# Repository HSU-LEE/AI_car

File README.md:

# AICAR — 라즈베리 파이 자율주행 미니카

카메라 한 대로 흰 차선을 따라가고, 교차로·횡단보도·신호등·레고 사람·장애물에 반응하며,
`course.py`에 적은 순서대로 경기 코스를 완주하는 자율주행 RC카입니다.
맥에서 메뉴를 더블클릭하거나 `aicar` 명령 하나로 코드 업로드, 주행, 보정, 녹화 분석을 모두 할 수 있습니다.

---

## 주요 기능

| 분야 | 내용 |
|---|---|
| **차선 주행** | 화면 아래를 여러 띠로 나눠 흰 선을 찾고, 위치·방향 오차로 조향각을 계산 (`bands` / `pairs` / `track` 방식) |
| **코스 실행** | 교차로, 차선 끝, 횡단보도, 차선 끊김을 만날 때마다 `course.py`의 다음 동작 실행 (좌회전, 우회전, 유턴, 정지 등) |
| **인식** | 신호등(빨강/초록), 횡단보도, 레고 사람(TFLite 신경망), 정지 지점, 거리 센서 장애물 |
| **시작 버튼** | GPIO21 버튼: 한 번 누르면 출발 → 일시정지 → 다시 출발, 3초 꾹 누르면 대기 상태로 |
| **출발 전 조향 확인** | 버튼으로 출발할 때 앞바퀴를 왼쪽 → 오른쪽 → 중앙으로 움직여 서보 상태를 확인 |
| **안전 장치** | 모터 감시(루프가 멈추면 정지), 별도 감시 프로세스(프로그램이 죽어도 모터 정지), 맥 연결이 끊겨도 주행 유지 |
| **브라우저 화면** | 주행 중 인식 결과를 `http://<파이 IP>:8000`에서 실시간 확인, 웹에서 신호등·횡단보도·선 등록 |
| **기록과 분석** | 모든 주행의 기록 자동 저장, 녹화 영상을 맥에서 다시 분석(`replay`), 폐루프 시뮬레이터(`sim.py`) |
| **자동 보정** | 경기장에서 트랙 색, 초점, 조명, 차선 폭, 소실점, 카메라 중심을 한 번에 측정·저장 |

## 시스템 구성

```mermaid
flowchart LR
    Mac["맥<br/>Menu.command · aicar"] -- "SSH / rsync" --> Pi
    Mac -. "브라우저 :8000" .-> Pi
    subgraph Pi["라즈베리 파이 4 (lane_follow.py)"]
        Cam["카메라"] --> Detect["차선·표지 인식"]
        Detect --> Course["코스 실행<br/>course.py"]
        Course --> Steer["조향 · 속도"]
    end
    Steer --> Servo["조향 서보<br/>GPIO18"]
    Steer --> Motor["구동 모터<br/>TB6612 · GPIO13/23/24"]
    Sensor["거리 센서<br/>GPIO17"] --> Course
    Button["시작 버튼<br/>GPIO21"] --> Course
```

## 하드웨어와 배선

| 부품 | 파이 핀 | 비고 |
|---|---|---|
| 조향 서보 신호 | GPIO18 (12번) | 하드웨어 PWM 50Hz |
| 모터 드라이버 TB6612 PWMA | GPIO13 (33번) | 하드웨어 PWM 20kHz |
| TB6612 AIN1 / AIN2 | GPIO23 (16번) / GPIO24 (18번) | 방향 |
| TB6612 STBY, VCC | 3.3V | GND 공통 |
| 거리 센서 Sharp GP2Y0A21 | GPIO17 (11번) | 5V 전원 |
| 시작 버튼 | GPIO21 (40번) ↔ GND (39번) | 내부 풀업 |
| 카메라 | CSI | Picamera2 |

하드웨어 PWM을 쓰려면 `/boot/firmware/config.txt`에 `dtoverlay=pwm-2chan,pin=18,func=2,pin2=13,func2=4`가 필요합니다.
SD 카드 이미지는 [`os-image/`](os-image)의 스크립트로 만듭니다.

## 빠르게 시작하기

1. 맥과 파이를 같은 Wi-Fi에 연결합니다. 파이의 핫스팟(`10.42.0.1`)에 붙어도 됩니다. 주소는 자동으로 찾습니다.
2. **`Menu.command`** 를 더블클릭하면 모든 기능이 한국어 메뉴로 나옵니다.
3. 터미널을 쓴다면:

```bash
./aicar status
```

```bash
./aicar calibrate
```

```bash
./aicar go
```

- `aicar status`: 연결과 파이 상태 확인
- `aicar calibrate`: 경기장에서 한 번 자동 보정 (직선 차로 가운데에 차를 놓고)
- `aicar go`: 주행 시작 (코드를 자동으로 올린 뒤 실행). 버튼을 켜 두었다면 버튼을 눌러야 출발합니다.

멈출 때는 터미널에서 `Ctrl+C`, 다른 창에서 `./aicar stop`, 또는 차의 버튼을 한 번 누릅니다.
전체 명령은 `./aicar help`로 볼 수 있습니다.

## 코스 작성

경기 코스는 [`pi/course.py`](pi/course.py)의 `COURSE` 목록에 순서대로 적습니다.
메뉴의 **자율주행 → 코스 편집**이나 `./aicar course`로 열 수 있고, 저장한 뒤 `./aicar push`(또는 다음 `go`) 때 파이에 올라갑니다.
VS Code를 쓴다면 [`tools/vscode-course`](tools/vscode-course)의 확장을 설치하면 자동 완성과 오류 표시를 쓸 수 있습니다.

```bash
python3 tools/vscode-course/install.py
```

자주 쓰는 스위치 (`course.py` 맨 위):

| 스위치 | 뜻 |
|---|---|
| `SPEED` | 기본 주행 속도 (0~1) |
| `SLOWDOWN_ON` | 교차로 접근·차선 놓침·회전 때 감속 여부 |
| `PERSON_ON`, `PERSON_AT` | 레고 사람 인식과 정지 위치 |
| `LANE_POINTS` | 차선 계산 방식 (`pairs` / `bands`) |

## 폴더 구조

```
AICAR/
├── Menu.command          한국어 메뉴 (더블클릭)
├── Drive.command 등      자주 쓰는 동작 바로 실행
├── aicar                 맥에서 쓰는 명령 도구 (연결, 업로드, 주행, 보정, 녹화)
├── Commands/             분야별 더블클릭 실행 파일 (수동, 자율주행, 카메라, 설정, 시스템)
├── Tune/                 인식 맞추기·보정 실행 파일
├── pi/                   파이에서 실행되는 코드
│   ├── lane_follow.py    주행 프로그램 (인식, 조향, 코스 실행, 브라우저 화면)
│   ├── course.py         경기 코스와 주행 스위치
│   ├── car.py            서보·모터 제어와 모터 안전 장치
│   ├── start_button.py   시작 버튼과 출발 전 조향 확인
│   ├── obstacle.py       거리 센서
│   ├── person.py         레고 사람 인식
│   ├── calibrate.py      자동 보정
│   ├── sim.py            폐루프 주행 시뮬레이터 (맥)
│   └── replay.py         녹화 재분석 (맥)
├── tests/test_vision.py  합성 영상으로 인식·코스·안전 로직 시험 (파이 없이)
├── tools/                녹화 비교, 시뮬레이터 평가, VS Code 코스 도우미
├── os-image/             SD 카드 이미지 만들기
└── cad/                  차체 Fusion 360 파일
```

## 시험

파이 없이 맥에서 인식, 코스 로직, 시작 버튼, 안전 장치를 시험합니다.

```bash
.venv/bin/python tests/test_vision.py
```

시뮬레이터로 여러 트랙을 달려 보고 차선 유지 성능을 비교할 수 있습니다.

```bash
.venv/bin/python pi/sim.py
```

## 안전

- 주행 루프가 0.5초 동안 명령을 보내지 않으면 모터를 멈춥니다.
- 주행 프로그램이 강제로 종료돼도, 따로 도는 감시 프로세스가 2초 안에 모터를 끕니다.
- 맥과의 연결이 끊겨도 주행은 계속됩니다. 이때는 차의 버튼을 눌러 일시정지하거나, 다시 연결해 `./aicar stop`을 실행합니다.
- 비밀번호와 기기별 보정값(`credentials.txt`, `pi/*.json`)은 저장소에 올리지 않습니다.

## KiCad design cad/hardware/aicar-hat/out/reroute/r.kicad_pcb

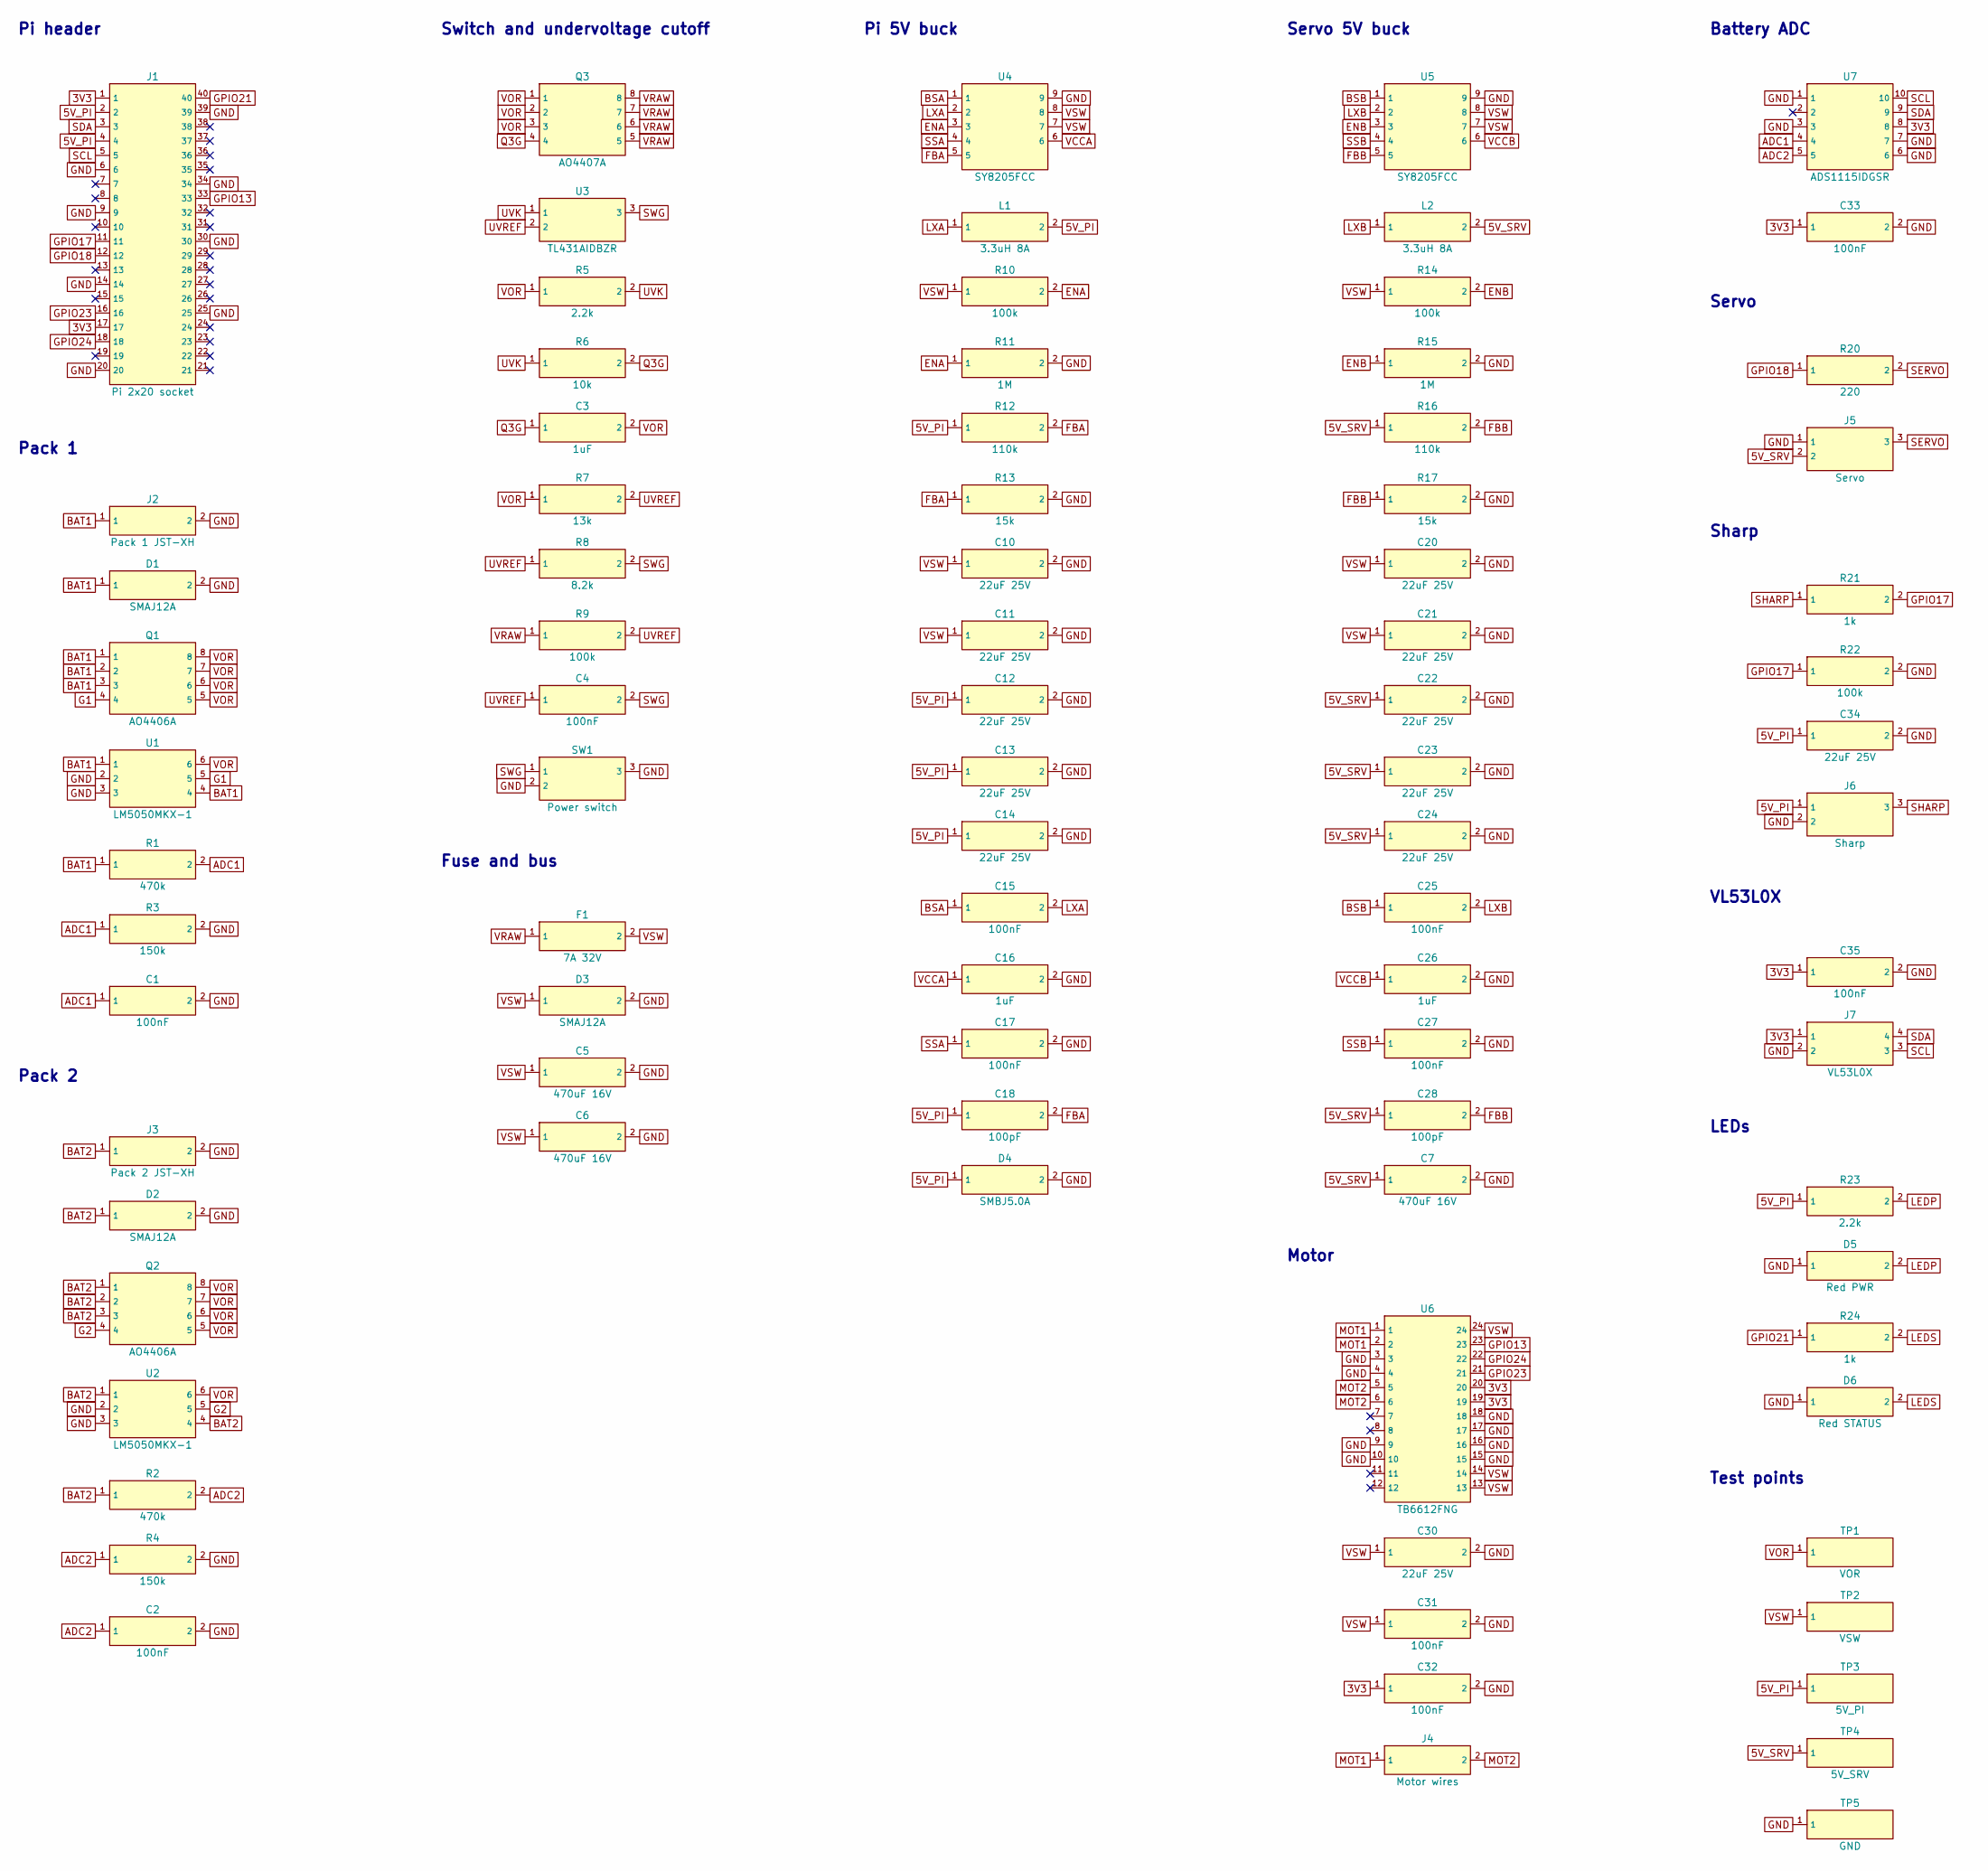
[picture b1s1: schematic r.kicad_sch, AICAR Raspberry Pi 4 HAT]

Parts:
C1, C2, C4, C15, C17, C25, C27, C31, C32, C33, C35: 100nF; C_0603_1608Metric; LCSC C1591
C3, C16, C26: 1uF; C_0603_1608Metric; LCSC C15849
C5, C6, C7: 470uF 16V; CP_Elec_8x10; LCSC C72517
C10, C11, C12, C13, C14, C20, C21, C22, C23, C24, C30, C34: 22uF 25V; C_1206_3216Metric; LCSC C12891
C18, C28: 100pF; C_0603_1608Metric; LCSC C14858
D1, D2, D3: SMAJ12A; D_SMA; LCSC C113957
D4: SMBJ5.0A; D_SMB; LCSC C113974
D5: Red PWR; LED_0603_1608Metric; LCSC C2286
D6: Red STATUS; LED_0603_1608Metric; LCSC C2286
F1: 7A 32V; Fuse_1206_3216Metric; LCSC C2924995
J1: Pi 2x20 socket; PinSocket_2x20_P2.54mm_Vertical
J2: Pack 1 JST-XH; JST_XH_B2B-XH-A_1x02_P2.50mm_Vertical
J3: Pack 2 JST-XH; JST_XH_B2B-XH-A_1x02_P2.50mm_Vertical
J4: Motor wires; SolderWire-0.5sqmm_1x02_P4.6mm_D0.9mm_OD2.1mm
J5: Servo; PinHeader_1x03_P2.54mm_Vertical
J6: Sharp; PinHeader_1x03_P2.54mm_Vertical
J7: VL53L0X; PinHeader_1x04_P2.54mm_Vertical
L1, L2: 3.3uH 8A; L_APV_APH0650; LCSC C49073675
Q1, Q2: AO4406A; SOIC-8_3.9x4.9mm_P1.27mm; LCSC C2944312
Q3: AO4407A; SOIC-8_3.9x4.9mm_P1.27mm; LCSC C2841482
R1, R2: 470k; R_0603_1608Metric; LCSC C23178
R3, R4: 150k; R_0603_1608Metric; LCSC C22807
R5, R23: 2.2k; R_0603_1608Metric; LCSC C4190
R6: 10k; R_0603_1608Metric; LCSC C25804
R7: 13k; R_0603_1608Metric; LCSC C22797
R8: 8.2k; R_0603_1608Metric; LCSC C25981
R9, R10, R14, R22: 100k; R_0603_1608Metric; LCSC C25803
R11, R15: 1M; R_0603_1608Metric; LCSC C22935
R12, R16: 110k; R_0603_1608Metric; LCSC C25805
R13, R17: 15k; R_0603_1608Metric; LCSC C22809
R20: 220; R_0603_1608Metric; LCSC C22962
R21, R24: 1k; R_0603_1608Metric; LCSC C21190
SW1: Power switch; PinHeader_1x03_P2.54mm_Vertical
TP1: VOR; TestPoint_Pad_D1.5mm
TP2: VSW; TestPoint_Pad_D1.5mm
TP3: 5V_PI; TestPoint_Pad_D1.5mm
TP4: 5V_SRV; TestPoint_Pad_D1.5mm
TP5: GND; TestPoint_Pad_D1.5mm
U1, U2: LM5050MKX-1; TSOT-23-6; LCSC C473393
U3: TL431AIDBZR; SOT-23; LCSC C23892
U4, U5: SY8205FCC; SOIC-8-1EP_3.9x4.9mm_P1.27mm_EP2.41x3.3mm; LCSC C111875
U6: TB6612FNG; SSOP-24_5.3x8.2mm_P0.65mm; LCSC C141517
U7: ADS1115IDGSR; MSOP-10_3x3mm_P0.5mm; LCSC C37593

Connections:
3V3: C32.1, C33.1, C35.1, J1.1, J1.17, J7.1, U6.19, U6.20, U7.8
5V_PI: C12.1, C13.1, C14.1, C18.1, C34.1, D4.1, J1.2, J1.4, J6.1, L1.2, R12.1, R23.1, TP3.1
5V_SRV: C7.1, C22.1, C23.1, C24.1, C28.1, J5.2, L2.2, R16.1, TP4.1
ADC1: C1.1, R1.2, R3.1, U7.4
ADC2: C2.1, R2.2, R4.1, U7.5
BAT1: D1.1, J2.1, Q1.1, Q1.2, Q1.3, R1.1, U1.1, U1.4
BAT2: D2.1, J3.1, Q2.1, Q2.2, Q2.3, R2.1, U2.1, U2.4
BSA: C15.1, U4.1
BSB: C25.1, U5.1
ENA: R10.2, R11.1, U4.3
ENB: R14.2, R15.1, U5.3
FBA: C18.2, R12.2, R13.1, U4.5
FBB: C28.2, R16.2, R17.1, U5.5
G1: Q1.4, U1.5
G2: Q2.4, U2.5
GND: C1.2, C2.2, C5.2, C6.2, C7.2, C10.2, C11.2, C12.2, C13.2, C14.2, C16.2, C17.2, C20.2, C21.2, C22.2, C23.2, C24.2, C26.2, C27.2, C30.2, C31.2, C32.2, C33.2, C34.2, C35.2, D1.2, D2.2, D3.2, D4.2, D5.1, D6.1, J1.6, J1.9, J1.14, J1.20, J1.25, J1.30, J1.34, J1.39, J2.2, J3.2, J5.1, J6.2, J7.2, R3.2, R4.2, R11.2, R13.2, R15.2, R17.2, R22.2, SW1.2, SW1.3, TP5.1, U1.2, U1.3, U2.2, U2.3, U4.9, U5.9, U6.3, U6.4, U6.9, U6.10, U6.15, U6.16, U6.17, U6.18, U7.1, U7.3, U7.6, U7.7
GPIO13: J1.33, U6.23
GPIO17: J1.11, R21.2, R22.1
GPIO18: J1.12, R20.1
GPIO21: J1.40, R24.1
GPIO23: J1.16, U6.21
GPIO24: J1.18, U6.22
LEDP: D5.2, R23.2
LEDS: D6.2, R24.2
LXA: C15.2, L1.1, U4.2
LXB: C25.2, L2.1, U5.2
MOT1: J4.1, U6.1, U6.2
MOT2: J4.2, U6.5, U6.6
Q3G: C3.1, Q3.4, R6.2
SCL: J1.5, J7.3, U7.10
SDA: J1.3, J7.4, U7.9
SERVO: J5.3, R20.2
SHARP: J6.3, R21.1
SSA: C17.1, U4.4
SSB: C27.1, U5.4
SWG: C4.2, R8.2, SW1.1, U3.3
UVK: R5.2, R6.1, U3.1
UVREF: C4.1, R7.2, R8.1, R9.2, U3.2
VCCA: C16.1, U4.6
VCCB: C26.1, U5.6
VOR: C3.2, Q1.5, Q1.6, Q1.7, Q1.8, Q2.5, Q2.6, Q2.7, Q2.8, Q3.1, Q3.2, Q3.3, R5.1, R7.1, TP1.1, U1.6, U2.6
VRAW: F1.1, Q3.5, Q3.6, Q3.7, Q3.8, R9.1
VSW: C5.1, C6.1, C10.1, C11.1, C20.1, C21.1, C30.1, C31.1, D3.1, F1.2, R10.1, R14.1, TP2.1, U4.7, U4.8, U5.7, U5.8, U6.13, U6.14, U6.24

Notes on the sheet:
Pi header
Pack 1
Pack 2
Switch and undervoltage cutoff
Fuse and bus
Pi 5V buck
Servo 5V buck
Motor
Battery ADC
Servo
Sharp
VL53L0X
LEDs
Test points

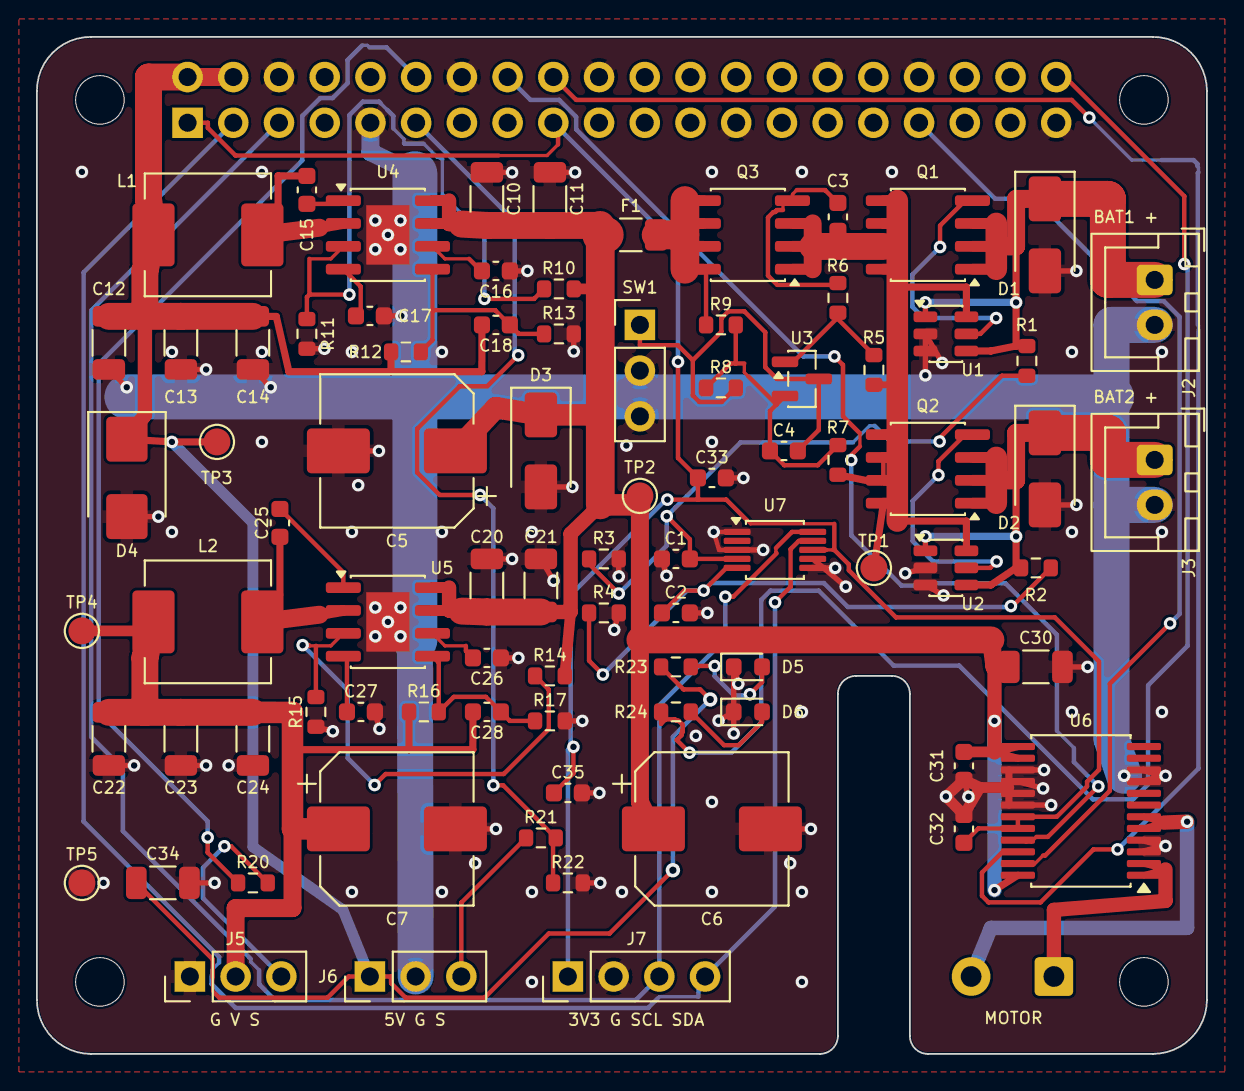
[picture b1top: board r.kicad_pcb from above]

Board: 2 copper layers, 65.0 x 56.5 mm, 89 parts (1 on the bottom side), 43 nets.

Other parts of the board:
H1, H2, H3, H4: MountingHole_2.7mm_M2.5

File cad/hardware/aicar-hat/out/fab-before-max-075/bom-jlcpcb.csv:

Comment,Designator,Footprint,LCSC Part #
SY8205FCC,"U4,U5",SOIC-8-1EP_3.9x4.9mm_P1.27mm_EP2.41x3.3mm,C111875
SMAJ12A,"D1,D2,D3",D_SMA,C113957
SMBJ5.0A,D4,D_SMB,C113974
22uF 25V,"C10,C11,C12,C13,C14,C20,C21,C22,C23,C24,C30,C34",C_1206_3216Metric,C12891
TB6612FNG,U6,SSOP-24_5.3x8.2mm_P0.65mm,C141517
100pF,"C18,C28",C_0603_1608Metric,C14858
1uF,"C16,C26,C3",C_0603_1608Metric,C15849
100nF,"C1,C15,C17,C2,C25,C27,C31,C32,C33,C35,C4",C_0603_1608Metric,C1591
1k,"R21,R24",R_0603_1608Metric,C21190
13k,R7,R_0603_1608Metric,C22797
150k,"R3,R4",R_0603_1608Metric,C22807
15k,"R13,R17",R_0603_1608Metric,C22809
Red PWR,D5,LED_0603_1608Metric,C2286
Red STATUS,D6,LED_0603_1608Metric,C2286
1M,"R11,R15",R_0603_1608Metric,C22935
220,R20,R_0603_1608Metric,C22962
470k,"R1,R2",R_0603_1608Metric,C23178
TL431AIDBZR,U3,SOT-23,C23892
100k,"R10,R14,R22,R9",R_0603_1608Metric,C25803
10k,R6,R_0603_1608Metric,C25804
110k,"R12,R16",R_0603_1608Metric,C25805
8.2k,R8,R_0603_1608Metric,C25981
AO4407A,Q3,SOIC-8_3.9x4.9mm_P1.27mm,C2841482
7A 32V,F1,Fuse_1206_3216Metric,C2924995
AO4406A,"Q1,Q2",SOIC-8_3.9x4.9mm_P1.27mm,C2944312
ADS1115IDGSR,U7,MSOP-10_3x3mm_P0.5mm,C37593
2.2k,"R23,R5",R_0603_1608Metric,C4190
LM5050MKX-1,"U1,U2",TSOT-23-6,C473393
3.3uH 8A,"L1,L2",L_APV_APH0650,C49073675
470uF 16V,"C5,C6,C7",CP_Elec_8x10,C72517

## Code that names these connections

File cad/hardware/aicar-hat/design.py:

"""AICAR HAT single source of truth: parts and nets.

gen_sch.py and gen_pcb.py both read this, so the schematic and board cannot disagree.
Part format: ref -> (value, footprint, lcsc, {pin: net}).
"""

R0603 = "Resistor_SMD:R_0603_1608Metric"
C0603 = "Capacitor_SMD:C_0603_1608Metric"
C1206 = "Capacitor_SMD:C_1206_3216Metric"
ELEC = "Capacitor_SMD:CP_Elec_8x10"
SO8 = "Package_SO:SOIC-8_3.9x4.9mm_P1.27mm"
SO8EP = "Package_SO:SOIC-8-1EP_3.9x4.9mm_P1.27mm_EP2.41x3.3mm"
TSOT6 = "Package_TO_SOT_SMD:TSOT-23-6"
SOT23 = "Package_TO_SOT_SMD:SOT-23"
SMB = "Diode_SMD:D_SMB"
SMA = "Diode_SMD:D_SMA"
WIRE_THIN = "Connector_Wire:SolderWire-0.5sqmm_1x02_P4.6mm_D0.9mm_OD2.1mm"
LED = "LED_SMD:LED_0603_1608Metric"
IND = "Inductor_SMD:L_APV_APH0650"
WIRE = "Connector_Wire:SolderWire-1sqmm_1x02_P5.4mm_D1.4mm_OD2.7mm"
XH2 = "Connector_JST:JST_XH_B2B-XH-A_1x02_P2.50mm_Vertical"
PIN3 = "Connector_PinHeader_2.54mm:PinHeader_1x03_P2.54mm_Vertical"
PIN4 = "Connector_PinHeader_2.54mm:PinHeader_1x04_P2.54mm_Vertical"
TP = "TestPoint:TestPoint_Pad_D1.5mm"

# Passive part numbers (0603; each number checked against its LCSC page).
RES = {"220": "C22962", "1k": "C21190", "2.2k": "C4190", "10k": "C25804", "8.2k": "C25981", "13k": "C22797",
       "15k": "C22809", "100k": "C25803", "110k": "C25805", "150k": "C22807",
       "470k": "C23178", "1M": "C22935"}
CAP = {"100pF": "C14858", "100nF": "C1591", "1uF": "C5199872"}
C22U = "C7432785"   # 22uF 25V X5R 1206.
C470U = "C72517"    # 470uF 16V 8x10 electrolytic.
TVS12 = "C113957"   # SMAJ12A.
TVS5 = "C113974"   # SMBJ5.0A.
FUSE = "C2924995"   # 7A 32V 1206 fast.

PARTS = {}


def add(ref, value, fp, lcsc, pins):
    PARTS[ref] = (value, fp, lcsc, {str(k): v for k, v in pins.items()})


def r(ref, value, a, b):
    add(ref, value, R0603, RES[value], {1: a, 2: b})


def c(ref, value, a, b):
    add(ref, value, C0603, CAP[value], {1: a, 2: b})


def c22(ref, a):
    add(ref, "22uF 25V", C1206, C22U, {1: a, 2: "GND"})


def elec(ref, a):
    add(ref, "470uF 16V", ELEC, C470U, {1: a, 2: "GND"})


# --- Raspberry Pi 40-pin socket (mounted on the bottom side). -----------------
GPIO = {1: "3V3", 17: "3V3", 2: "5V_PI", 4: "5V_PI", 3: "SDA", 5: "SCL",
        11: "GPIO17", 12: "GPIO18", 16: "GPIO23", 18: "GPIO24", 33: "GPIO13", 40: "GPIO21"}
for n in (6, 9, 14, 20, 25, 30, 34, 39):
    GPIO[n] = "GND"
add("J1", "Pi 2x20 socket", "Connector_PinSocket_2.54mm:PinSocket_2x20_P2.54mm_Vertical", "",
    {n: GPIO.get(n, "") for n in range(1, 41)})

# --- Battery inputs: JST-XH, TVS, ideal diode, voltage divider. ------------
for i, (jr, dr, ur, qr) in enumerate((("J2", "D1", "U1", "Q1"), ("J3", "D2", "U2", "Q2")), 1):
    bat, gate = f"BAT{i}", f"G{i}"
    add(jr, f"Pack {i} JST-XH", XH2, "", {1: bat, 2: "GND"})
    add(dr, "SMAJ12A", SMA, TVS12, {1: bat, 2: "GND"})
    add(ur, "LM5050MKX-1", TSOT6, "C473393",
        {1: bat, 2: "GND", 3: "GND", 4: bat, 5: gate, 6: "VOR"})
    add(qr, "AO4406A", SO8, "C2944312",
        {1: bat, 2: bat, 3: bat, 4: gate, 5: "VOR", 6: "VOR", 7: "VOR", 8: "VOR"})
    r(f"R{i}", "470k", bat, f"ADC{i}")
    r(f"R{i + 2}", "150k", f"ADC{i}", "GND")
    c(f"C{i}", "100nF", f"ADC{i}", "GND")

# --- Power switch and undervoltage cutoff: off near 6.0V, on above 6.8V. -------
add("Q3", "AO4407A", SO8, "C2841482",
    {1: "VOR", 2: "VOR", 3: "VOR", 4: "Q3G", 5: "VRAW", 6: "VRAW", 7: "VRAW", 8: "VRAW"})
add("U3", "TL431AIDBZR", SOT23, "C23892", {1: "UVK", 2: "UVREF", 3: "SWG"})
r("R5", "2.2k", "VOR", "UVK")
r("R6", "10k", "UVK", "Q3G")     # 10 ms gate ramp with C3: soft start, rides out hot-swap dips.
c("C3", "1uF", "Q3G", "VOR")
r("R7", "13k", "VOR", "UVREF")
r("R8", "8.2k", "UVREF", "SWG")
r("R9", "100k", "VRAW", "UVREF")
c("C4", "100nF", "UVREF", "SWG")
add("SW1", "Power switch", "Connector_PinHeader_2.54mm:PinHeader_1x03_P2.54mm_Vertical", "",
    {1: "SWG", 2: "GND", 3: "GND"})     # Middle pin is the common; the off-side throw just stays at GND.

# --- Fuse and main bus. --------------------------------------------------------
add("F1", "7A 32V", "Fuse:Fuse_1206_3216Metric", FUSE, {1: "VRAW", 2: "VSW"})
add("D3", "SMAJ12A", SMA, TVS12, {1: "VSW", 2: "GND"})
elec("C5", "VSW")
elec("C6", "VSW")

# --- 5V bucks: one for the Pi, one for the servo. ------------------------------
for tag, ic, out, l, parts in (
        ("A", "U4", "5V_PI", "L1", ("C10", "C11", "C12", "C13", "C14", "C15", "C16", "C17", "C18")),
        ("B", "U5", "5V_SRV", "L2", ("C20", "C21", "C22", "C23", "C24", "C25", "C26", "C27", "C28"))):
    rs = {"A": ("R10", "R11", "R12", "R13"), "B": ("R14", "R15", "R16", "R17")}[tag]
    add(ic, "SY8205FCC", SO8EP, "C111875",
        {1: f"BS{tag}", 2: f"LX{tag}", 3: f"EN{tag}", 4: f"SS{tag}", 5: f"FB{tag}", 6: f"VCC{tag}",
         7: "VSW", 8: "VSW", 9: "GND"})
    add(l, "3.3uH 8A", IND, "C49073675", {1: f"LX{tag}", 2: out})
    r(rs[0], "100k", "VSW", f"EN{tag}")
    r(rs[1], "1M", f"EN{tag}", "GND")
    r(rs[2], "110k", out, f"FB{tag}")   # Vout = 0.6 * (1 + 110k / 15k) = 5.0V.
    r(rs[3], "15k", f"FB{tag}", "GND")
    c22(parts[0], "VSW")
    c22(parts[1], "VSW")
    c22(parts[2], out)
    c22(parts[3], out)
    c22(parts[4], out)
    c(parts[5], "100nF", f"BS{tag}", f"LX{tag}")
    c(parts[6], "1uF", f"VCC{tag}", "GND")
    c(parts[7], "100nF", f"SS{tag}", "GND")
    c(parts[8], "100pF", out, f"FB{tag}")
add("D4", "SMBJ5.0A", SMB, TVS5, {1: "5V_PI", 2: "GND"})    # Blows F1 if the Pi buck shorts high.
elec("C7", "5V_SRV")

# --- Motor driver: channel A only. Unused channel B inputs tied low. ------------
TB = {1: "MOT1", 2: "MOT1", 5: "MOT2", 6: "MOT2", 3: "GND", 4: "GND", 9: "GND", 10: "GND",
      7: "", 8: "", 11: "", 12: "", 13: "VSW", 14: "VSW", 24: "VSW", 15: "GND", 16: "GND", 17: "GND",
      18: "GND", 19: "3V3", 20: "3V3", 21: "GPIO23", 22: "GPIO24", 23: "GPIO13"}
add("U6", "TB6612FNG", "Package_SO:SSOP-24_5.3x8.2mm_P0.65mm", "C141517", TB)
c22("C30", "VSW")
c("C31", "100nF", "VSW", "GND")
c("C32", "100nF", "3V3", "GND")
add("J4", "Motor wires", WIRE_THIN, "", {1: "MOT1", 2: "MOT2"})

# --- Battery ADC: 0x48 (ADDR to GND). -------------------------------------------
add("U7", "ADS1115IDGSR", "Package_SO:MSOP-10_3x3mm_P0.5mm", "C37593",
    {1: "GND", 2: "", 3: "GND", 4: "ADC1", 5: "ADC2", 6: "GND", 7: "GND", 8: "3V3", 9: "SDA", 10: "SCL"})
c("C33", "100nF", "3V3", "GND")

# --- Servo. ----------------------------------------------------------------------
r("R20", "220", "GPIO18", "SERVO")
add("J5", "Servo", "Connector_PinHeader_2.54mm:PinHeader_1x03_P2.54mm_Vertical", "",
    {1: "GND", 2: "5V_SRV", 3: "SERVO"})

# --- Sharp GP2Y0A21: red 5V, black GND, yellow Vo. --------------------------------
r("R21", "1k", "SHARP", "GPIO17")
r("R22", "100k", "GPIO17", "GND")   # Reads clear when the sensor is unplugged.
c22("C34", "5V_PI")
add("J6", "Sharp", PIN3, "",
    {1: "5V_PI", 2: "GND", 3: "SHARP"})

# --- VL53L0X: VIN must stay 3.3V because the module pulls I2C up to VIN. ------------
c("C35", "100nF", "3V3", "GND")
add("J7", "VL53L0X", PIN4, "",
    {1: "3V3", 2: "GND", 3: "SCL", 4: "SDA"})

# --- Status LEDs. --------------------------------------------------------------------
r("R23", "2.2k", "5V_PI", "LEDP")
add("D5", "Red PWR", LED, "C2286", {1: "GND", 2: "LEDP"})
r("R24", "1k", "GPIO21", "LEDS")
add("D6", "Red STATUS", LED, "C2286", {1: "GND", 2: "LEDS"})

# --- Test points. ---------------------------------------------------------------------
for ref, net in (("TP1", "VOR"), ("TP2", "VSW"), ("TP3", "5V_PI"), ("TP4", "5V_SRV"), ("TP5", "GND")):
    add(ref, net, TP, "", {1: net})

GROUPS = [
    ("Pi header", ["J1"]),
    ("Pack 1", ["J2", "D1", "Q1", "U1", "R1", "R3", "C1"]),
    ("Pack 2", ["J3", "D2", "Q2", "U2", "R2", "R4", "C2"]),
    ("Switch and undervoltage cutoff", ["Q3", "U3", "R5", "R6", "C3", "R7", "R8", "R9", "C4", "SW1"]),
    ("Fuse and bus", ["F1", "D3", "C5", "C6"]),
    ("Pi 5V buck", ["U4", "L1", "R10", "R11", "R12", "R13", "C10", "C11", "C12", "C13", "C14",
                    "C15", "C16", "C17", "C18", "D4"]),
    ("Servo 5V buck", ["U5", "L2", "R14", "R15", "R16", "R17", "C20", "C21", "C22", "C23", "C24",
                       "C25", "C26", "C27", "C28", "C7"]),
    ("Motor", ["U6", "C30", "C31", "C32", "J4"]),
    ("Battery ADC", ["U7", "C33"]),
    ("Servo", ["R20", "J5"]),
    ("Sharp", ["R21", "R22", "C34", "J6"]),
    ("VL53L0X", ["C35", "J7"]),
    ("LEDs", ["R23", "D5", "R24", "D6"]),
    ("Test points", ["TP1", "TP2", "TP3", "TP4", "TP5"]),
]
